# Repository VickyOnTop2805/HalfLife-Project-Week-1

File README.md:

<div align="center">

<h1>Starbie - My First PCB Project</h1>

<p><strong>Hack Club Half Life | Week 1 - PCB Design</strong></p>

<p>
  My first attempt at designing a custom circuit board,
  learning electronics, and figuring out KiCad along the way.
</p>

</div>

<hr>

<h2>About the Project</h2>

<p>
Starbie is my first PCB design project, which I made for Hack Club
Half Life Week 1. The idea is to create a small digital pet that
can interact with people through buttons, sensors and an OLED display.
</p>

<p>
Before starting this project, I had some basic coding knowledge,
but I had never designed a PCB before. I didn't understand how
KiCad worked, what footprints were, or how a schematic could be
turned into an actual circuit board.
</p>

<p>
I decided to follow the Starbie starter project because it seemed
like a good way to learn electronics without needing physical parts
straight away.
</p>

<p>
I used KiCad 10 on my Mac to create the schematic, arrange the PCB,
route the copper tracks, add a ground plane and export the
manufacturing files.
</p>

<p>
This project was definitely more complicated than I expected.
There were several times when I got confused about what I was
doing, but I kept going and eventually managed to complete the
main PCB design.
</p>

<p>
The physical device hasn't been built yet. This repository
documents the PCB design stage and everything I learned.
</p>

<hr>

<h2>Why I Chose Starbie</h2>

<p>
I wanted to make something more interesting than a basic circuit
with an LED that turns on and off.
</p>

<p>
A digital pet sounded interesting because it combines different
electronic components into one project.
</p>

<p>
Starbie could eventually show different expressions, react to
movement, respond to button presses and display information
about its surroundings.
</p>

<p>
I also liked that I could start with a PCB design and later
turn it into an actual physical device.
</p>

<p>
Since I had never used KiCad before, following the starter
guide seemed like a reasonable way to learn.
</p>

<hr>

<h2>Project Goals</h2>

<ul>
  <li>Learn how KiCad works.</li>
  <li>Understand schematic symbols and PCB footprints.</li>
  <li>Create a circuit using the XIAO ESP32-C3.</li>
  <li>Add two physical buttons.</li>
  <li>Connect an OLED display.</li>
  <li>Include a motion sensor.</li>
  <li>Include a temperature and humidity sensor.</li>
  <li>Learn how to route copper tracks.</li>
  <li>Add a ground copper zone.</li>
  <li>Understand PCB design-rule checking.</li>
  <li>Export Gerber and drill files.</li>
  <li>Create a bill of materials.</li>
  <li>Document everything on GitHub.</li>
</ul>

<hr>

<h2>Components</h2>

<table>
  <tr>
    <th>Component</th>
    <th>Quantity</th>
    <th>Purpose</th>
  </tr>
  <tr>
    <td>Seeed Studio XIAO ESP32-C3</td>
    <td>1</td>
    <td>Main microcontroller</td>
  </tr>
  <tr>
    <td>0.96-inch OLED Display</td>
    <td>1</td>
    <td>Displays Starbie's face and animations</td>
  </tr>
  <tr>
    <td>MPU6050 Motion Sensor</td>
    <td>1</td>
    <td>Detects movement and tilting</td>
  </tr>
  <tr>
    <td>DHT11 Sensor</td>
    <td>1</td>
    <td>Measures temperature and humidity</td>
  </tr>
  <tr>
    <td>Push Buttons</td>
    <td>2</td>
    <td>Controls Starbie's interactions</td>
  </tr>
  <tr>
    <td>10k Ohm Resistor</td>
    <td>1</td>
    <td>DHT11 data pull-up resistor</td>
  </tr>
  <tr>
    <td>4-pin Header</td>
    <td>1</td>
    <td>OLED connection</td>
  </tr>
  <tr>
    <td>8-pin Header</td>
    <td>1</td>
    <td>MPU6050 connection</td>
  </tr>
  <tr>
    <td>Custom 2-layer PCB</td>
    <td>1 design</td>
    <td>Connects all the components</td>
  </tr>
</table>

<h3>XIAO ESP32-C3</h3>

<p>
The XIAO ESP32-C3 is the main controller for Starbie.
It will eventually run the code that controls the sensors,
buttons and OLED display.
</p>

<p>
One of the first things I had to learn was how to identify
its different pins.
</p>

<p>
Initially, labels like GND, VBUS, 3V3_OUT, D1, D2 and D3
were confusing because I wasn't familiar with how
microcontroller pins worked.
</p>

<p>
I learned that each pin has a particular function and that
connecting the wrong pins can cause serious problems.
</p>

<h3>OLED Display</h3>

<p>
The OLED screen will act as Starbie's face.
My plan is to display different expressions and animations.
</p>

<p>
I added a four-pin connector for the OLED.
It uses I2C communication through SDA and SCL.
</p>

<p>
I learned that SDA carries data while SCL provides
the clock signal for communication.
</p>

<h3>MPU6050 Motion Sensor</h3>

<p>
The MPU6050 can measure acceleration and angular motion.
I included it so Starbie can eventually react when someone
tilts or shakes the device.
</p>

<p>
It also uses I2C, which means it can share the SDA and SCL
communication lines with the OLED.
</p>

<h3>DHT11 Sensor</h3>

<p>
The DHT11 measures temperature and humidity.
I added it because I wanted Starbie to react to its
environment rather than only button presses.
</p>

<p>
I also added a 10k ohm pull-up resistor to the data line.
This helped me learn why some digital signals need
pull-up resistors.
</p>

<h3>Push Buttons</h3>

<p>
I added two push buttons to control Starbie.
They are connected to the ESP32's GPIO pins and ground.
</p>

<p>
I plan to use the buttons to change expressions,
switch modes or interact with Starbie.
</p>

<hr>

<h2>Software and Tools</h2>

<h3>KiCad 10</h3>

<p>
KiCad was the main software I used for this project.
I used it for:
</p>

<ul>
  <li>Creating the schematic</li>
  <li>Importing custom libraries</li>
  <li>Assigning footprints</li>
  <li>Arranging PCB components</li>
  <li>Routing tracks</li>
  <li>Adding the ground plane</li>
  <li>Running electrical and design-rule checks</li>
  <li>Exporting Gerber and drill files</li>
</ul>

<p>
The interface was overwhelming at first because there
were so many menus, tools and layers.
</p>

<p>
After spending time using it, I gradually started understanding
how the different editors worked together.
</p>

<h3>GitHub</h3>

<p>
I used GitHub to store my project files, bill of materials,
journal and documentation.
</p>

<h3>Hack Club Lapse</h3>

<p>
I used Lapse to record my PCB design process.
It helped me document my actual working sessions
and show how the project developed.
</p>

<hr>

<h2>My Design Process</h2>

<h3>1. Creating the Project</h3>

<p>
I started by installing KiCad 10 on my Mac and
creating a project called Starbie-PCB.
</p>

<p>
At first, I even had trouble creating a new project
because I didn't understand the template selection window.
</p>

<p>
Once I got past that, I opened the Schematic Editor
and started working on the circuit.
</p>

<h3>2. Importing the Custom Libraries</h3>

<p>
The Starbie care package contained symbols, footprints
and 3D models for the components.
</p>

<p>
I initially didn't understand what these files were
or how to import them into KiCad.
</p>

<p>
I had trouble with KiCad's library tables and had
to configure the project-specific libraries.
</p>

<p>
This was one of my first major challenges.
</p>

<p>
Eventually, I managed to import the XIAO ESP32-C3 symbol
and footprint.
</p>

<h3>3. Creating the Schematic</h3>

<p>
After importing the libraries, I started creating the schematic.
</p>

<p>
I placed the XIAO ESP32-C3 first, followed by the power
and ground symbols.
</p>

<p>
I then added two push buttons, the OLED connector,
the MPU6050 connector, the DHT11 sensor and a resistor.
</p>

<p>
I connected the components according to their
intended GPIO and communication signals.
</p>

<p>
One thing I learned was that it's important to
check the actual pin names instead of assuming
a connection is correct just because the wire
looks like it's connected.
</p>

<hr>

<h2>My First Major Mistake</h2>

<p>
One of the biggest mistakes I made was accidentally
connecting the 3.3V power line to GND.
</p>

<p>
At the time, I was still learning how KiCad's wiring
tool worked.
</p>

<p>
The connection points were close together, and I
connected the power wire to the wrong pin.
</p>

<p>
After looking at the schematic more carefully,
I realised the mistake and removed the incorrect wire.
</p>

<p>
I then connected the 3.3V symbol to the correct pin.
</p>

<p>
This taught me how important it is to check
the electrical connections carefully.
</p>

<p>
It was also a reminder that even a tiny mistake
in a schematic can become a much bigger problem
if the physical PCB is manufactured.
</p>

<hr>

<h2>Understanding Footprints</h2>

<p>
This was probably one of the most confusing parts
of the project.
</p>

<p>
When I opened the footprint assignment window,
I saw a huge list of libraries and component names.
</p>

<p>
I didn't understand why I needed footprints when
I had already placed the components in the schematic.
</p>

<p>
I eventually learned the difference:
</p>

<ul>
  <li>
    A schematic symbol represents the electrical
    connections of a component.
  </li>
  <li>
    A PCB footprint represents its physical pads
    and dimensions.
  </li>
</ul>

<p>
I assigned footprints to all the components,
including the ESP32-C3, buttons, connectors,
resistor and DHT11.
</p>

<p>
I also learned that the actual parts need to
match the footprints before manufacturing.
</p>

<hr>

<h2>Moving to the PCB Editor</h2>

<p>
After completing the schematic, I transferred
the components into PCB Editor.
</p>

<p>
At first, everything appeared grouped together
with thin lines connecting different pads.
</p>

<p>
I learned that these lines are called ratsnest lines.
They show the electrical connections that still
need to be routed.
</p>

<p>
I arranged the components around the board,
keeping the XIAO ESP32-C3 near the centre.
</p>

<p>
I placed the buttons toward one side,
the OLED connector near the top and the
other components around the remaining space.
</p>

<p>
I moved and rotated components several times
before settling on a layout.
</p>

<p>
I also had to think about the USB connector
and making sure it would be accessible.
</p>

<hr>

<h2>Routing the PCB</h2>

<p>
Routing was another completely new experience.
</p>

<p>
I learned that copper tracks connect the
different components electrically.
</p>

<p>
I used KiCad's routing tool to connect
the pads based on the schematic.
</p>

<p>
At first, I wasn't sure how to turn corners
or avoid crossing other tracks.
</p>

<p>
As I continued working, I became more
comfortable with the routing tool.
</p>

<p>
I learned that component placement can make
routing easier or harder.
</p>

<p>
After completing the routing, KiCad showed
zero unrouted connections.
</p>

<p>
This was one of the best moments of the
project because I could finally see
the completed circuit board layout.
</p>

<hr>

<h2>Adding the Ground Plane</h2>

<p>
After routing the PCB, I added a ground
copper zone on the B.Cu layer.
</p>

<p>
Before this project, I didn't really
understand what a ground plane was.
</p>

<p>
I learned that a copper-filled area can
provide a shared ground connection
across the board.
</p>

<p>
I selected the back copper layer,
created a zone assigned to GND,
drew its boundary and filled it.
</p>

<p>
At first, the settings were confusing
because there were options for clearance,
minimum width and thermal reliefs.
</p>

<p>
Eventually, I got the copper zone filled
and could see the back copper area.
</p>

<hr>

<h2>Design Rule Checking</h2>

<p>
After routing the PCB, I used KiCad's
Design Rules Checker, also called DRC.
</p>

<p>
The first check reported 19 warnings.
</p>

<p>
Initially, I was worried that I had
made a lot of mistakes.
</p>

<p>
After looking through the warnings,
I realised that most of them involved
silkscreen graphics on the XIAO footprint.
</p>

<p>
Some graphics overlapped solder-mask openings
around the pads.
</p>

<p>
I investigated the warnings and modified
the footprint graphics.
</p>

<p>
After making the changes, I reduced
the warning count from 19 to one.
</p>

<h3>Latest DRC Results</h3>

<table>
  <tr>
    <th>Check</th>
    <th>Result</th>
  </tr>
  <tr>
    <td>Errors</td>
    <td>0</td>
  </tr>
  <tr>
    <td>Warnings</td>
    <td>1</td>
  </tr>
  <tr>
    <td>Unconnected Items</td>
    <td>0</td>
  </tr>
  <tr>
    <td>Schematic Parity Issues</td>
    <td>0</td>
  </tr>
</table>

<p>
The remaining warning says that the XIAO
footprint on the PCB differs from the
library version.
</p>

<p>
I believe this is related to the silkscreen
changes I made, but I still need to verify
the footprint dimensions and pad numbering
before manufacturing.
</p>

<p>
Getting zero errors and zero unrouted
connections was a major milestone for me.
</p>

<hr>

<h2>Exporting the Gerber Files</h2>

<p>
Once the design was routed, I exported
the manufacturing files.
</p>

<p>
I learned that PCB manufacturers use
Gerber files to understand the
different layers of the board.
</p>

<p>
These files describe things like:
</p>

<ul>
  <li>Front copper</li>
  <li>Back copper</li>
  <li>Front solder mask</li>
  <li>Back solder mask</li>
  <li>Silkscreen</li>
  <li>Board outline</li>
</ul>

<p>
I also generated the drill files,
which describe the holes in the PCB.
</p>

<p>
After exporting everything, I opened
the files using KiCad's Gerber Viewer.
</p>

<p>
At first, the different coloured layers
overlapping each other were confusing.
</p>

<p>
I figured out how to hide individual
layers so I could inspect them separately.
</p>

<p>
I checked the copper tracks, pads,
drill holes and board outline.
</p>

<p>
This helped me understand how PCB designs
are prepared for manufacturing.
</p>

<hr>

<h2>Bill of Materials</h2>

<p>
I also created a bill of materials,
usually called a BOM.
</p>

<p>
The BOM lists the parts needed to
assemble the physical Starbie.
</p>

<p>
I searched for suppliers and compared
prices for the components.
</p>

<p>
My original parts list was more expensive,
so I looked for cheaper options.
</p>

<p>
One example was finding a lower-priced
XIAO ESP32-C3 from Seeed Studio.
</p>

<p>
I learned that the lowest component price
doesn't always mean the lowest total cost.
</p>

<p>
Shipping, taxes and minimum order
quantities also matter.
</p>

<p>
The BOM is an initial purchasing plan.
I still need to verify shipping and
component compatibility.
</p>

<hr>

<h2>Problems I Encountered</h2>

<details>
<summary><strong>Problem 1 - Library Setup</strong></summary>

<p>
I had trouble getting KiCad to recognise
the custom symbol and footprint libraries.
</p>

<p>
I learned how project-specific libraries
work and how to configure their file paths.
</p>

</details>

<details>
<summary><strong>Problem 2 - Footprint Assignment</strong></summary>

<p>
I didn't initially understand the difference
between symbols and footprints.
</p>

<p>
After learning what each one represents,
I was able to assign the footprints
to the components.
</p>

</details>

<details>
<summary><strong>Problem 3 - Incorrect Power Connection</strong></summary>

<p>
I accidentally connected 3.3V to GND.
</p>

<p>
I removed the incorrect connection
and rewired the schematic.
</p>

</details>

<details>
<summary><strong>Problem 4 - PCB Routing</strong></summary>

<p>
I initially found it difficult to route
tracks without crossing other connections.
</p>

<p>
Moving components and learning the routing
tool made the process easier.
</p>

</details>

<details>
<summary><strong>Problem 5 - DRC Warnings</strong></summary>

<p>
My first DRC check reported 19 warnings.
</p>

<p>
Most were caused by silkscreen graphics
overlapping solder-mask openings.
</p>

<p>
I modified the footprint graphics
and reduced the warnings to one.
</p>

</details>

<hr>

<h2>What I Learned</h2>

<p>
Before starting Starbie, I thought PCB
design mainly involved connecting
components together.
</p>

<p>
Now I understand that there are
several different stages.
</p>

<ol>
  <li>Create the schematic.</li>
  <li>Choose the correct components.</li>
  <li>Assign matching footprints.</li>
  <li>Arrange the physical layout.</li>
  <li>Route the copper tracks.</li>
  <li>Add copper zones where needed.</li>
  <li>Run design checks.</li>
  <li>Export manufacturing files.</li>
  <li>Verify the parts and manufacturing requirements.</li>
</ol>

<p>
I also learned that troubleshooting
is a big part of electronics.
</p>

<p>
A lot of my time wasn't spent drawing
the circuit. It was spent understanding
problems and figuring out how to fix them.
</p>

<p>
This project made me more confident
about learning new technical tools.
</p>

<hr>

<hr>

<h2>Designing My Custom Starbie Logo</h2>

<h3>Why I Wanted to Make a Logo</h3>

<p>
After spending so much time designing the actual PCB, I wanted
to do something a little more creative and give Starbie its own
identity. Until this point, most of my work involved schematics,
footprints, copper tracks, and fixing errors in KiCad.
</p>

<p>
I realised that even though the circuit board was mostly finished,
I didn't really have anything that made the project visually
recognisable as Starbie.
</p>

<p>
Since Starbie is supposed to be a cute little digital pet,
I wanted the logo to reflect that personality rather than
looking like a serious electronics company logo.
</p>

<p>
My idea was to combine a friendly star character with
elements that represent electronics and space.
I wanted someone looking at the logo to understand
that Starbie is supposed to be playful, interactive,
and a little futuristic.
</p>

<h3>The Logo Design</h3>

<p>
For the main design, I chose a smiling star character
because the name Starbie immediately made me think
of stars and space.
</p>

<p>
I wanted the character to look friendly, with
expressive eyes and a happy face, because the
actual device is intended to behave like a digital pet.
</p>

<p>
I also included small stars, orbit-like shapes,
and circuit-board-inspired lines around the name.
The circuit traces connect the design back to the
electronics side of the project.
</p>

<p>
I kept the design mostly monochrome so that it
could potentially be adapted for the PCB silkscreen,
where simple lines and high contrast are useful.
</p>

<h3>My Starbie Logo</h3>

<div align="center">

  <p>
    <em>
      My custom Starbie logo, featuring a smiling star mascot,
      space-inspired details, and electronic circuit patterns.
    </em>
  </p>

</div>

<h3>What I Wanted the Logo to Represent</h3>

<p>
I wanted the logo to represent the main idea behind
the project: combining technology with personality.
</p>

<p>
The star character represents Starbie itself,
while the circuit patterns represent the PCB
and electronics that make the project possible.
</p>

<p>
The orbit shapes add a space theme and make
the design more playful.
</p>

<p>
I also wanted it to feel like something that
could eventually be printed on the device's
enclosure or used as an icon for the firmware.
</p>

<h3>Challenges With the Logo</h3>

<p>
One thing I had to think about was the difference
between designing a logo for a screen and designing
something that might eventually go on a PCB.
</p>

<p>
A detailed logo can look good when viewed at
a large size, but it might become difficult
to recognise when reduced to a tiny area.
</p>

<p>
PCB silkscreen printing also has limitations.
Very small lines, text, and details may not
appear clearly after manufacturing.
</p>

<p>
Because of this, I want to experiment with
making a simpler version of the logo that
could fit on the PCB without overlapping
pads, tracks, or important component labels.
</p>

<p>
The full logo would be better suited for
the GitHub README, project documentation,
and possibly a future enclosure.
</p>

<h3>How Long I Spent on the Logo</h3>

<p>
I spent around 58 minutes working on the
logo design and thinking about how it
should represent Starbie.
</p>

<p>
I honestly didn't expect the visual side
of the project to take that much thought.
After spending hours on the circuit board,
I thought making a logo would be the easy part.
</p>

<p>
But I realised there were quite a few
things to consider, including the character,
lettering, overall composition, and how
the design would work at different sizes.
</p>

<p>
It was a nice change from troubleshooting
KiCad, and I enjoyed having something
more creative to work on.
</p>

<h3>How I Plan to Use the Logo</h3>

<p>
I would like to use the logo in several
parts of the Starbie project.
</p>

<ul>
  <li>As the main image in my GitHub README.</li>
  <li>On the project documentation and progress updates.</li>
  <li>As inspiration for a simpler PCB silkscreen design.</li>
  <li>On a future 3D-printed enclosure.</li>
  <li>As a possible startup image or branding element for Starbie.</li>
</ul>

<h3>What I Learned</h3>

<p>
Working on the logo made me realise that
building a project isn't only about making
the electronics work.
</p>

<p>
Presentation and design are important too,
especially when the goal is to create
something that people will interact with.
</p>

<p>
I also learned that a design made for a
computer screen isn't automatically suitable
for manufacturing.
</p>

<p>
Before putting this logo directly onto the
PCB, I would need to simplify it, check
the minimum line widths, and make sure
it fits in an appropriate area.
</p>

<p>
I'm happy that Starbie now has a visual
identity to go along with the electronic
design. It makes the whole project feel
more personal to me.
</p>

<h2>My Custom Starbie Logo</h2>

<div align="center">

  <p>
    <em>
      My custom logo for Starbie, featuring a smiling
      star character and circuit-inspired details.
    </em>
  </p>
</div>
<hr>

<h2>What I Would Improve</h2>

<h3>Component Compatibility</h3>

<p>
I want to verify the exact dimensions
and pinouts of the OLED, MPU6050,
buttons and XIAO ESP32-C3.
</p>

<h3>Silkscreen Labels</h3>

<p>
I would like to improve the printed
labels so the connectors are easier
to identify when assembling the board.
</p>

<h3>Component Placement</h3>

<p>
I want to check the physical clearance
around the sensors and display.
</p>

<h3>Documentation</h3>

<p>
I want to add more screenshots showing
the schematic, PCB layout and design checks.
</p>

<h3>Testing</h3>

<p>
Once the physical PCB is manufactured,
I want to test the connections and
make sure the components work correctly.
</p>

<hr>

<h2>Future Plans</h2>

<p>
The next goal is to turn Starbie
into a working physical device.
</p>

<p>
I want to:
</p>

<ul>
  <li>Verify all component footprints.</li>
  <li>Get the PCB manufactured.</li>
  <li>Assemble the components.</li>
  <li>Program the ESP32-C3.</li>
  <li>Display expressions on the OLED.</li>
  <li>Add button interactions.</li>
  <li>Detect shaking and tilting.</li>
  <li>Display temperature and humidity.</li>
  <li>Experiment with simple animations.</li>
  <li>Design an enclosure for the PCB.</li>
</ul>

<hr>

<h2>Project Status</h2>

<table>
  <tr>
    <th>Task</th>
    <th>Status</th>
  </tr>
  <tr>
    <td>Create KiCad Project</td>
    <td>Completed</td>
  </tr>
  <tr>
    <td>Import Libraries</td>
    <td>Completed</td>
  </tr>
  <tr>
    <td>Create Schematic</td>
    <td>Completed</td>
  </tr>
  <tr>
    <td>Assign Footprints</td>
    <td>Completed</td>
  </tr>
  <tr>
    <td>Arrange PCB Components</td>
    <td>Completed</td>
  </tr>
  <tr>
    <td>Route Copper Tracks</td>
    <td>Completed</td>
  </tr>
  <tr>
    <td>Add Ground Plane</td>
    <td>Completed</td>
  </tr>
  <tr>
    <td>Run DRC</td>
    <td>Completed - 1 warning remains</td>
  </tr>
  <tr>
    <td>Export Gerber Files</td>
    <td>Completed</td>
  </tr>
  <tr>
    <td>Inspect Gerber Files</td>
    <td>Completed</td>
  </tr>
  <tr>
    <td>Create BOM</td>
    <td>Initial version completed</td>
  </tr>
  <tr>
    <td>Verify Physical Components</td>
    <td>Still to do</td>
  </tr>
  <tr>
    <td>Assemble PCB</td>
    <td>Not started</td>
  </tr>
  <tr>
    <td>Program Starbie</td>
    <td>Not started</td>
  </tr>
</table>

<hr>

<h2>Project Files</h2>

<ul>
  <li><code>Starbie-PCB.kicad_pro</code> - KiCad project</li>
  <li><code>Starbie-PCB.kicad_sch</code> - Schematic</li>
  <li><code>Starbie-PCB.kicad_pcb</code> - PCB layout</li>
  <li><code>Gerbers/</code> - Manufacturing files</li>
  <li><code>BOM.md</code> - Bill of materials</li>
  <li><code>JOURNAL.md</code> - Development journal</li>
</ul>

<hr>

<h2>Project Screenshots</h2>

<p>
This section will contain screenshots
of my design process.
</p>

<h3>Schematic</h3>
<p>Add schematic screenshot here.</p>

<h3>PCB Layout</h3>
<p>Add PCB layout screenshot here.</p>

<h3>Ground Plane</h3>
<p>Add ground plane screenshot here.</p>

<h3>DRC Results</h3>
<p>Add DRC screenshot here.</p>

<h3>Gerber Viewer</h3>
<p>Add Gerber Viewer screenshot here.</p>

<hr>

<h2>Development Timelapse</h2>

<p>
I recorded part of my development process
using Hack Club Lapse.
</p>

<p>
<a href="https://lapse.hackclub.com/timelapse/-okA6pEqrZLI">
Watch my Starbie development timelapse
</a>
</p>

<hr>

<h2>Final Thoughts</h2>

<p>
This project took much longer than I
expected when I first started.
</p>

<p>
I spent around five and a half hours
working through KiCad and trying
to understand everything.
</p>

<p>
I was so focused on finishing the
PCB that I continued working
through dinner without getting up.
</p>

<p>
There were moments when I honestly
had no idea what I was supposed
to do next.
</p>

<p>
The most difficult parts were
importing the libraries,
understanding footprints,
routing the PCB and fixing
the design warnings.
</p>

<p>
But each problem helped me
learn something new.
</p>

<p>
The best part was finally
seeing the PCB fully routed
with zero unconnected items.
</p>

<p>
Even though the physical
device hasn't been built yet,
I'm happy that I managed
to complete my first PCB design.
</p>

<p>
If I were starting again,
I would spend more time
checking component footprints
before routing the board.
</p>

<p>
I'm looking forward to
the next stage and hopefully
turning Starbie into a
working digital pet.
</p>

<hr>

<div align="center">

<p>
<strong>Made for Hack Club Half Life - Week 1</strong>
</p>

<p>
My first PCB design, and definitely not my last.
</p>

</div>

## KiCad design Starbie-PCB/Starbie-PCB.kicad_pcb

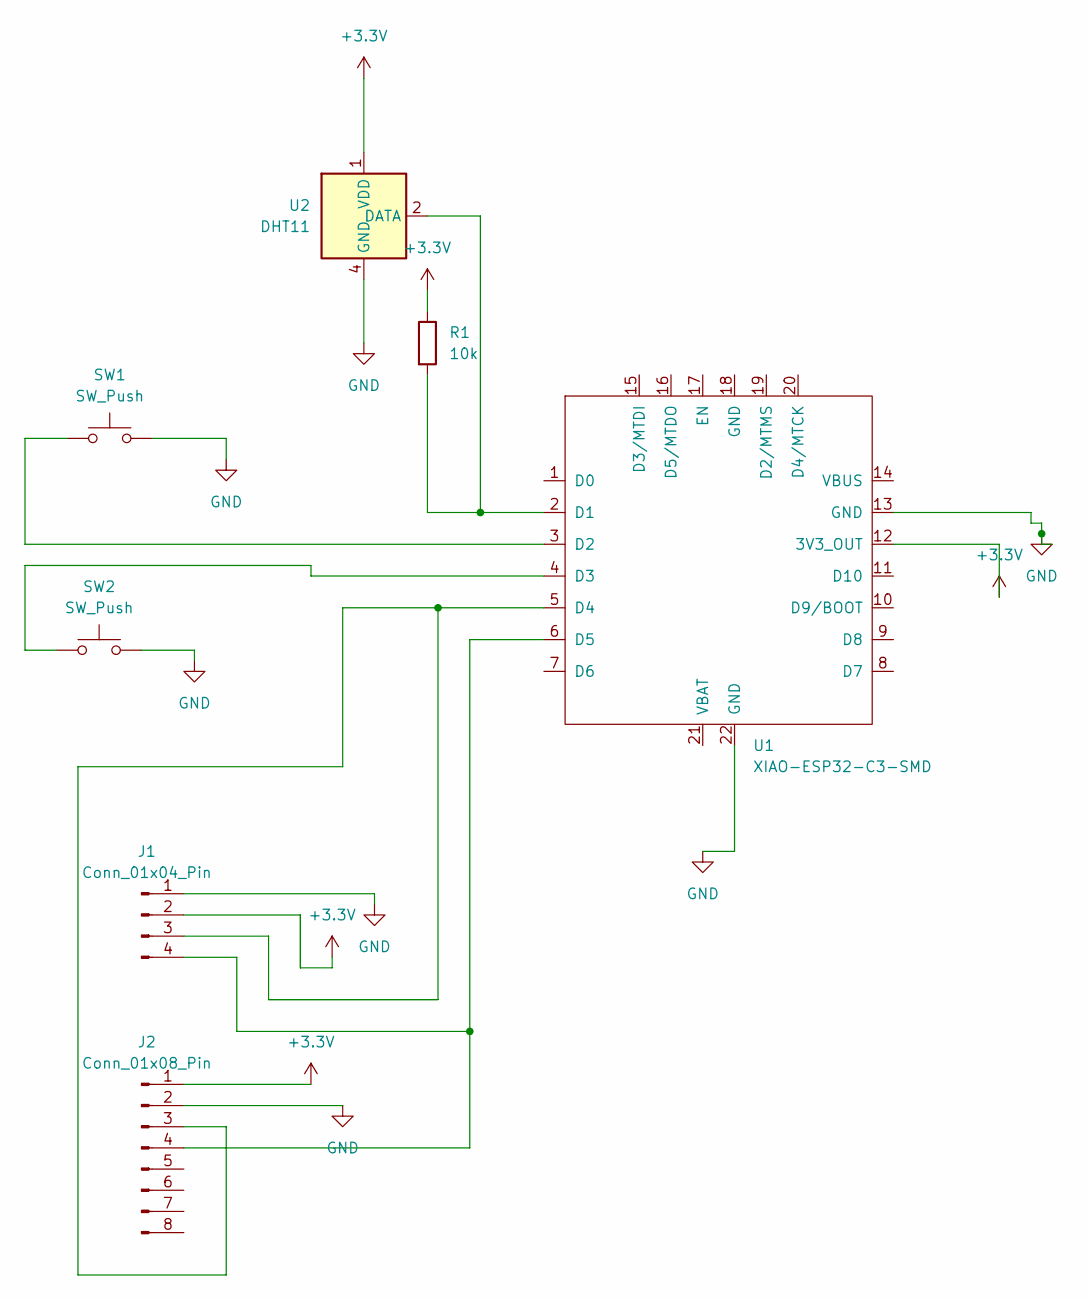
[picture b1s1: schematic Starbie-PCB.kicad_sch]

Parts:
J1: Conn_01x04_Pin; PinHeader_1x04_P2.54mm_Vertical
J2: Conn_01x08_Pin; PinHeader_1x08_P2.54mm_Vertical
R1: 10k; R_0805_2012Metric
SW1, SW2: SW_Push; SW_PUSH_6mm
U1: XIAO-ESP32-C3-SMD
U2: DHT11; Aosong_DHT11_5.5x12.0_P2.54mm

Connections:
+3.3V: J1.2, J2.1, R1.1, U1.12 (3V3_OUT), U2.1 (VDD)
GND: J1.1, J2.2, SW1.2, SW2.2, U1.13 (GND), U1.22 (GND), U2.4 (GND)
unnamed: J1.3, J2.3, U1.5 (D4)
unnamed: J1.4, J2.4, U1.6 (D5)
unnamed: R1.2, U1.2 (D1), U2.2 (DATA)
unnamed: SW1.1, U1.3 (D2)
unnamed: SW2.1, U1.4 (D3)

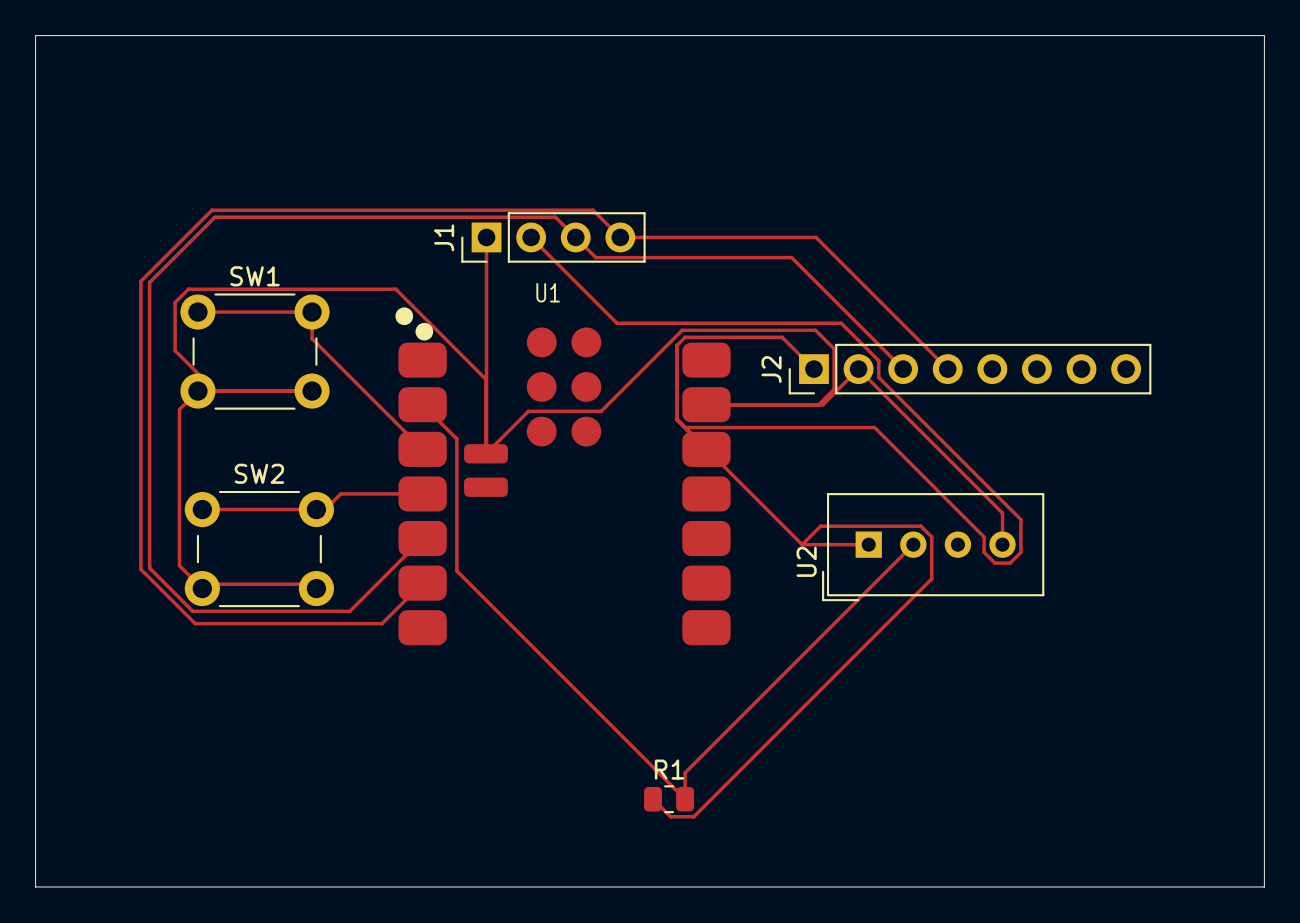
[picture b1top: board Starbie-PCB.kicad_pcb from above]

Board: 2 copper layers, 70.0 x 48.5 mm, 7 parts (0 on the bottom side), 7 nets.
